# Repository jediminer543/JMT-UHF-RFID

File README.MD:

# The UHF-RFID project

This project aims to do build a working UHF RFID reader (ISO 18000-6C thing) using a pair of CC1101s.

But why the hell would you want to do this? Simple. The silicon to do UHF RFID tag reading goes for around $30 per chip in low volumes, dropping to $20 in high volumes. The entire main devboard, fully assembled, cost a grand total of $10 per board.

Given the anciliary components (MCU, Antennas, PowerRegs, PowerAmps, etc.) are likely to cost that again, BOM Cost for a reader built with this scheme is likely $20-30 total, which even at a 2.5x profit maring would still be competetive with the cheapest readers avalible on sites like Aliexpress.

## But why do you care?

UHF RFID allows for the reading of passive tags at up to 15m ranges for some tags. 15m would happen to helpfully cover most houses.

Further depending on which research you look at, these tags have localisability to below 10cm.

Combining these two features, if a many reader system were viable and cheap, it could make losing things a thing of the past. Or just make sure that places stay tidy

## Project state

I have the boards fabbed and assembled; I need to get some more RF stuff fabbed but it's just striplines so should be cheap to make.

Successful communication to the tags was achieved, but return linking failed due to the requirement for a circulator esque device, which has been designed acording to the specifications of [this paper](https://www.researchgate.net/publication/224684549_A_Passive_Circulator_for_RFID_Application_with_High_Isolation_using_a_Directional_Coupler) and simulated with QUCS. These still need to be fabricated.

The code for the project is very much unoptimised; spending far too long doing bitsetting, but this was done intentionally for ease of tweaking; future software improvements will occur if/when the project progresses.

## Why is this on github?

Two reasons. Firstly to share with the world so someone else can hopefully learn or develop something from it

Secondly, because I'm applying for some jobs and saying "here's a thing I made and the source for it" seems fun.

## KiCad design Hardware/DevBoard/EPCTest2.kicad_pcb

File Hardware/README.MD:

## Hardware stuff

The devboard folder contains all the files used for the creation of the current devboard, including JLC assemblable gerbers.

The circulator folder contains the files for the circulator in theory, but the results have yet to be validated in the real world

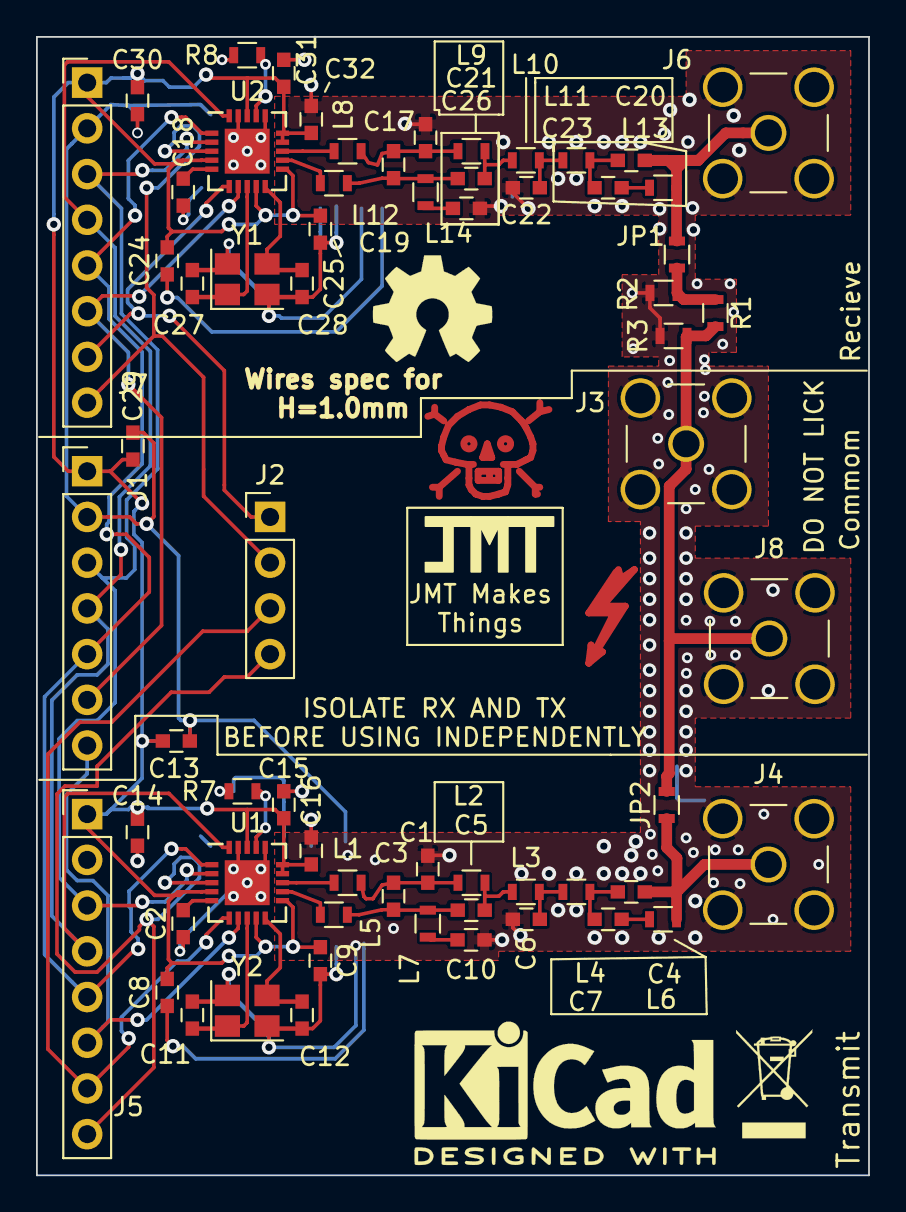
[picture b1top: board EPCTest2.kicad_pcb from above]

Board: 2 copper layers, 46.2 x 63.2 mm, 70 parts (0 on the bottom side), 41 nets.

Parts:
 : WEEE; WEEE-Logo_4.2x6mm_SilkScreen
 #2: KiCad; KiCad-Logo2_8mm_SilkScreen
 #3: DANGER; Symbol_Danger_CopperTop_Small
 #4: OSHW; OSHW-Symbol_6.7x6mm_SilkScreen
C1, C5, C17, C21: 1.5pF; C_0603
C2, C18: 100nF; C_0603
C3, C19: 1pF; C_0603
C4, C20: 12pF; C_0603
C6, C22: 3.3pF; C_0603
C7, C23: 47pF; C_0603
C8, C9, C13, C14, C15, C16, C24, C25, C29, C30, C31, C32: DC; C_0603
C10, C26: 100pF; C_0603
C11, C12, C27, C28: 27pF; C_0603
DO NOT LICK: Zap; Symbol_Highvoltage_Type1_CopperTop_Small
J1: CommonSPI; Pin_Header_Straight_1x07_Pitch2.54mm
J2: GDO; Pin_Header_Straight_1x04_Pitch2.54mm
J3: CombOut; SMA_THT_Jack_Straight
J4, J6: Local RF Out; SMA_THT_Jack_Straight
J5, J7: DigitalIO; Pin_Header_Straight_1x08_Pitch2.54mm
J8: Amped In; SMA_THT_Jack_Straight
JP1: ISO_RX; R_0603
JP2: ISO_TX; R_0603
L1, L3, L4, L5, L8, L10, L11, L12: 12nH; L_0603
L2, L7, L9, L14: 18nH; L_0603
L6, L13: 3.3nH; L_0603
R1: PICross; R_0603
R2, R3: PILeg; R_0603
R7, R8: 56K; R_0603
U1, U2: CC1101; QFN-20-1EP_4x4mm_Pitch0.5mm
Y1, Y2: 26Mhz; Crystal_SMD_3225-4pin_3.2x2.5mm

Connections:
+3V3: C8.1, C9.1, C13.1, C14.1, C15.1, C16.1, C24.1, C25.1, C29.1, C30.1, C31.1, C32.1, J1.1, J5.1, J7.1, U1.4, U1.9, U1.11, U1.14, U1.15, U1.18, U2.4, U2.9, U2.11, U2.14, U2.15, U2.18
/CSnRX: J1.6, J7.6, U2.7
/CSnTX: J1.7, J5.6, U1.7
/GDO0_RX: J2.1, J7.7, U2.6
/GDO0_TX: J2.3, J5.7, U1.6
/GDO2_RX: J2.2, J7.8, U2.3
/GDO2_TX: J2.4, J5.8, U1.3
/MISO: J1.3, J5.3, J7.3, U1.2, U2.2
/MOSI: J1.4, J5.4, J7.4, U1.20, U2.20
/RFLeft/DCOUPL: C18.2, U2.5
/RFLeft/RBIAS: R8.2, U2.17
/RFLeft/RF1_N: C17.2, C19.1, L8.2, L9.1
/RFLeft/RF1_P: C19.2, C21.2, L12.1, L14.1
/RFLeft/RF_N: L8.1, U2.13
/RFLeft/RF_P: L12.2, U2.12
/RFLeft/RF_SE: C20.2, J6.1, JP1.1, L13.1
/RFLeft/XOSC1: C27.1, U2.8, Y1.1
/RFLeft/XOSC2: C28.1, U2.10, Y1.3
/RFRight/DCOUPL: C2.2, U1.5
/RFRight/RBIAS: R7.2, U1.17
/RFRight/RF1_N: C1.2, C3.1, L1.2, L2.1
/RFRight/RF1_P: C3.2, C5.2, L5.1, L7.1
/RFRight/RF_N: L1.1, U1.13
/RFRight/RF_P: L5.2, U1.12
/RFRight/RF_SE: C4.2, J4.1, JP2.1, L6.1
/RFRight/XOSC1: C11.1, U1.8, Y2.1
/RFRight/XOSC2: C12.1, U1.10, Y2.3
/RF_RX: JP1.2, R1.1, R2.2
/RF_RX_ATT: J3.1, J8.1, JP2.2, R1.2, R3.2
/SCLK: J1.5, J5.5, J7.5, U1.1, U2.1
GND: C1.1, C2.1, C6.2, C8.2, C9.2, C10.2, C11.2, C12.2, C13.2, C14.2, C15.2, C16.2, C17.1, C18.1, C22.2, C24.2, C25.2, C26.2, C27.2, C28.2, C29.2, C30.2, C31.2, C32.2, J1.2, J3.2, J4.2, J5.2, J6.2, J7.2, J8.2, R2.1, R3.1, R7.1, R8.1, U1.16, U1.19, U1.21, U2.16, U2.19, U2.21, Y1.2, Y1.4, Y2.2, Y2.4
unnamed: C4.1, C7.2, L4.2
unnamed: C5.1, L2.2, L3.1
unnamed: C6.1, L3.2, L4.1
unnamed: C7.1, L6.2
unnamed: C10.1, L7.2
unnamed: C20.1, C23.2, L11.2
unnamed: C21.1, L9.2, L10.1
unnamed: C22.1, L10.2, L11.1
unnamed: C23.1, L13.2
unnamed: C26.1, L14.2

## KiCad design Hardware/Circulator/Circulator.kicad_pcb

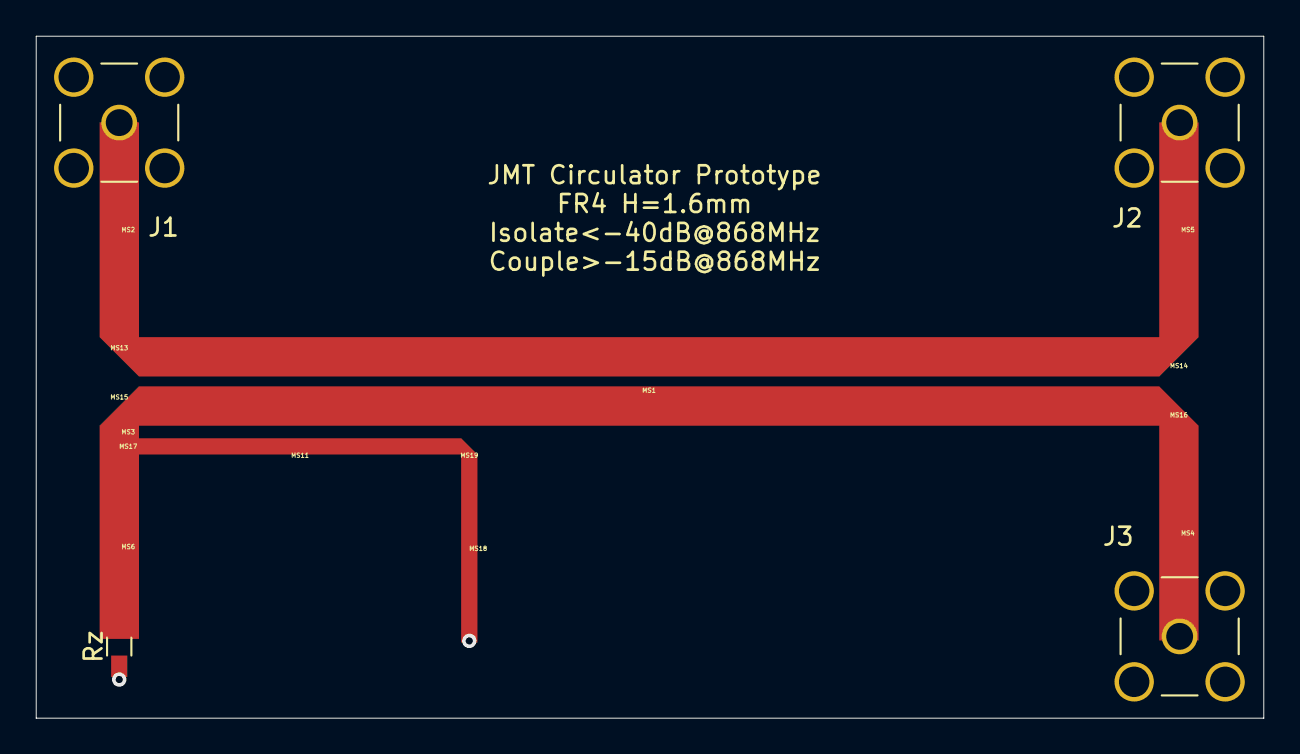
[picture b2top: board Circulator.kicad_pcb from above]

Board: 2 copper layers, 68.6 x 38.1 mm, 18 parts (0 on the bottom side), 2 nets.

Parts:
J1, J2, J3: Conn_Coaxial; SMA_THT_Jack_Straight
MS1: microstrip_coupled_lines; MCOUPLED
MS2, MS3, MS4, MS5, MS6, MS11, MS18: microstrip_line; MLIN
MS13, MS14, MS15, MS16, MS19: microstrip_mittered_bend; MMBEND
MS17: microstrip_tee; MTEE
Rz: Rz; R_0603_HandSoldering

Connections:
GND: J1.2, J2.2, J3.1, J3.2, Rz.1
unnamed: J1.1, J2.1

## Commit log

2021-08-20 Uploading all current work
